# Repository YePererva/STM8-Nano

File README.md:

# STM8-Nano
 STM8 development board with Arduino Nano form factor and USB Type C

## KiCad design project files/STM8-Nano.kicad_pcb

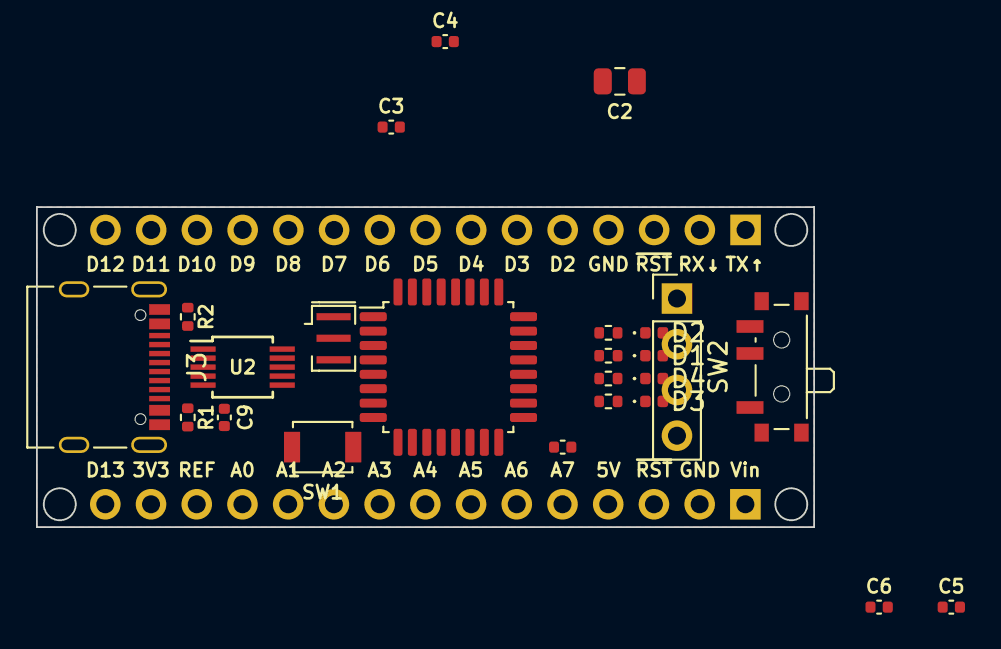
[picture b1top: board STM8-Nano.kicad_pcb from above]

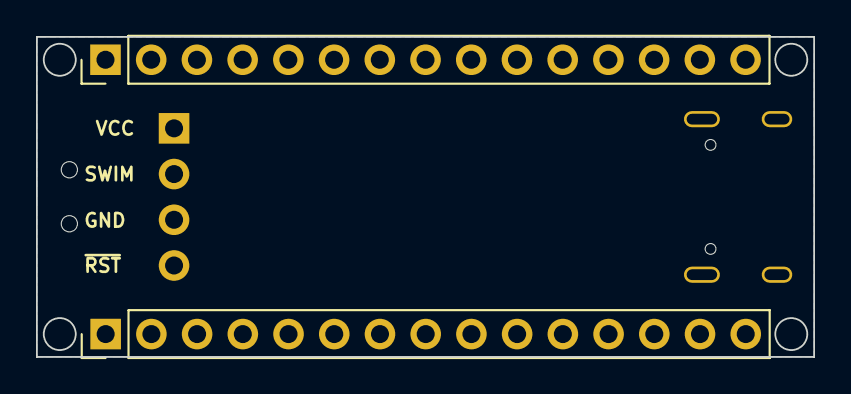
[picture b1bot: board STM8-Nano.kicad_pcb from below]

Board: 2 copper layers, 43.2 x 17.8 mm, 26 parts (2 on the bottom side), 22 nets, no tracks yet.

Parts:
C1, C3, C4, C6: 100nF; C_0402_1005Metric
C2: 2.2uF; C_0805_2012Metric
C5: 1uF; C_0402_1005Metric
C9: 10uF; C_0402_1005Metric
D1: RX; LED_0402_1005Metric
D2: TX↓; LED_0402_1005Metric
D3: D13; LED_0402_1005Metric
D4: PWR; LED_0402_1005Metric
J1: RIGHT; PinHeader_1x15_P2.54mm_Vertical
J2: LEFT; PinHeader_1x15_P2.54mm_Vertical
J3: USB_C_Receptacle_USB2.0; USB_C_Receptacle_Palconn_UTC16-G
J4: SWIM; PinHeader_1x04_P2.54mm_Vertical
R1, R2: 5.1K; R_0402_1005Metric
R3, R4: 10K; R_0402_1005Metric
R5, R6: 1K; R_0402_1005Metric
SW1: RESET; SW_SPST_B3U-1000P
SW2: VCC; SW_SPDT_PCM12
U1: STM8F105K4; LQFP-32_7x7mm_P0.8mm
U2: CH340E; MSOP-10_3x3mm_P0.5mm
Y1: 16MHZ; Resonator_SMD_Murata_CSTxExxV-3Pin_3.0x1.1mm

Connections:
+5V: J2.4, SW2.3 (C), U2.7 (VCC)
/D0/RX: J1.2, R3.2, U2.8 (TXD)
/D1/TX: J1.1, R4.2, U2.9 (RXD)
/D13: J2.15, R5.2
/~RST: C1.1, C9.2, J1.3, J2.3, J4.4, SW1.2, U1.1 (NRST)
GND: C1.2, C2.2, C3.1, C4.1, C5.1, C6.1, J1.4, J2.2, J3.A1 (GND), J3.A12 (GND), J3.B1 (GND), J3.B12 (GND), J4.3, R1.2, R2.2, R6.2, SW1.1, U1.4 (VSS), U2.3 (GND), Y1.2
unnamed: C2.1, U1.5 (VCAP)
unnamed: C3.2, U2.10 (V3)
unnamed: C9.1, U2.4 (~RTS)
unnamed: D1.1 (K), R3.1
unnamed: D2.1 (K), R4.1
unnamed: D3.1 (K), R5.1
unnamed: D4.1 (K), R6.1
unnamed: J3.A5 (CC1), R2.1
unnamed: J3.B5 (CC2), R1.1
PA1: J1.10, U1.2 (PA1), Y1.1
PA2: J1.11, U1.3 (PA2), Y1.3
SWIM: J4.2, U1.26 (PD1)
USB(+): J3.A6 (D+), J3.B6 (D+), U2.1 (UD+)
USB(-): J3.A7 (D-), J3.B7 (D-), U2.2 (UD-)
VBUS: J3.A4 (VBUS), J3.A9 (VBUS), J3.B4 (VBUS), J3.B9 (VBUS)
VCC: C4.2, C5.2, C6.2, D1.2 (A), D2.2 (A), D3.2 (A), D4.2 (A), J4.1, SW2.2 (B), U1.6 (VDD), U1.7 (VDDIO)

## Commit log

2022-07-30 files rearrangement
2022-07-30 references update
2022-07-30 added annotation
2022-07-31 case change
2022-09-18 LED moved
